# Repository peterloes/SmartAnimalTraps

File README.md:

# SmartAnimalTraps
Electrical applications for non-deadly animal traps built up with intelligent radio module, drive electronics for servomotors
(flap drive) and drive electronics for different low power light barriers.

Author: Loës P. (2022) 

## 1 RadiomoduleV1.0 & electronicsLightbarriers & electronicsServo
- Radio module V1.0 add-on board (not illustrated)
- Electronic light barriers for different distances.
- Servomotor and shutter is adjusted to the end positions.

The radio handheld transmitter is able to open and close the shutter by pressing a button.

Light barrier 1 and light barrier 2 are connected with logic AND. Both light barriers needs a falling edge of the signals to close the shutter. 
Light barrier 1 and light barrier 2 is forbidden to open the shutter.

Pushbutton 1 and pushbutton 2, mounted on the top of the electronical circuit, are able to open and close the shutter.

### Current consumption:

Standby 20.8mA@6V, clocked approx. 2.0mA@6V (after 10 minutes).

Operate mode 320mA@6V (max.)

### Application bird trap:

### Components:

https://github.com/peterloes/SmartAnimalTraps/blob/main/Getting_Started_Tutorial/13_wireless_radiomodule.JPG

https://github.com/peterloes/SmartAnimalTraps/blob/main/Schematics/radio_module_V1.0.brd.pdf

https://github.com/peterloes/Light_Barrier

https://github.com/peterloes/Servo_Engine

--> Protection against misuse!!! Dear follower, please contact me via email to get more information about the used wireless radio module. 

## 2 RadiomoduleV2.0 & electronicsServo
- Radio module V2.0 add-on board (not illustrated) 
- No light barriers
- Servomotor and shutter is adjusted to the end positions.

The radio handheld transmitter is able to open and close the shutter by pressing a button.

Pushbutton 1 and pushbutton 2, mounted on the top of the electronical circuit, are able to open and close the shutter.

### Current consumption:  

Standby 20.5mA@6V, clocked approx. 2.3mA@6V (after 10 minutes).

Operate mode 235mA@6V (max.)

### Components:

https://github.com/peterloes/SmartAnimalTraps/blob/main/Getting_Started_Tutorial/13_wireless_radiomodule.JPG

https://github.com/peterloes/SmartAnimalTraps/blob/main/Schematics/radio_module_V2.0.brd.pdf

https://github.com/peterloes/Servo_Engine

--> Protection against misuse!!! Dear follower, please contact me via email to get more information about the used wireless radio module. 

## 3 RadiomoduleV3.0 & modifiedServo
- Radio module V3.0 add-on board (Version from year 2010, to revision)
- No light barriers
- Full rotation of modified servomotor --> Motor rotation 360° --> left/right rotations

The radio handheld transmitter is able to open, close and to rotates the shutter by pressing a button.

### Current consumption:  

Standby 30mA@6V, clocked approx. 11.4mA@6V (after 10 minutes). With LEDs.

Operate mode 179mA@6V Motor is steady turning. With LEDs.

### Application:

https://github.com/peterloes/SmartAnimalTraps/blob/main/Getting_Started_Tutorial/Snaptrap.jpg

### Components:

https://github.com/peterloes/SmartAnimalTraps/blob/main/Getting_Started_Tutorial/13_wireless_radiomodule.JPG

https://github.com/peterloes/SmartAnimalTraps/blob/main/Schematics/radio_module_V3.0.brd.pdf

https://github.com/peterloes/SmartAnimalTraps/blob/main/Getting_Started_Tutorial/33_Servo_modified.JPG

https://github.com/peterloes/SmartAnimalTraps/blob/main/Getting_Started_Tutorial/34_old_batterypack.JPG

--> Protection against misuse!!! Dear follower, please contact me via email to get more information about the used wireless radio module. 

## 4 RadiomoduleV4.0 & reusedFrontplate & electronicsLightbarriers & electronicsServo
- Radio module V4.0 add-on board (not illustrated)
- Reused frontplate from nestbox included light barriers.
- Electronic light barriers.
- Servomotor and shutter is adjusted to the end positions.

The radio handheld transmitter is able to open and close the shutter by pressing a button.

Light barrier 1 and light barrier 2 are connected with logic AND. Both light barriers needs a falling edge of the signals to close the shutter.
Light barrier 1 and light barrier 2 is forbidden to open the shutter.

Pushbutton 1 and pushbutton 2, mounted on the top of the electronical circuit, are able to open and close the shutter.

### Current consumption:

Standby 21.9mA@6V, clocked approx. 3.5mA@6V (after 10 minutes). With LEDs.

Operate mode 303mA@6V (max.). With LEDs.

### Components:

https://github.com/peterloes/SmartAnimalTraps/blob/main/Getting_Started_Tutorial/13_wireless_radiomodule.JPG

https://github.com/peterloes/SmartAnimalTraps/blob/main/Schematics/radio_module_V4.0.brd.pdf

https://github.com/peterloes/Light_Barrier

https://github.com/peterloes/Servo_Engine

Frontplate nestbox

https://github.com/peterloes/RFID-MS

https://github.com/peterloes/SmartAnimalTraps/blob/main/Getting_Started_Tutorial/7_Supplier.txt

--> Protection against misuse!!! Dear follower, please contact me via email to get more information about the used wireless radio module. 

## 5 ElectronicsLightBarriers & electronicsServo
- No radio module
- Electronic light barriers for different distances are switching shutter positions.
- Servomotor and shutter is adjusted to the end positions.

Light barrier 1 or light barrier 2 are able to open or to close the shutter.

Pushbutton 1 or pushbutton 2, mounted on the top of the electronical circuit, are able to open or to close the shutter.

### Current consumption:

Standby 0,22mA@6V --> 220µA@6V

Operate mode 322mA@6V (max.)

### Components:

https://github.com/peterloes/Light_Barrier

https://github.com/peterloes/Servo_Engine

## 6 ReusedFrontplate & electronicsServo
- No radio module
- Reused frontplate from nestbox included light barriers. Switching shutter positions.
- Servomotor and shutter is adjusted to the end positions.

Light barrier 1 or light barrier 2 are able to open or to close the shutter.

Pushbutton 1 or pushbutton 2, mounted on the top of the electronical circuit, are able to open or to close the shutter.

### Current consumption:

Standby 0,05mA@6V --> 50µA@6V

Operate mode 375mA@6V (max.)

### Components:

https://github.com/peterloes/Servo_Engine

Frontplate nestbox

https://github.com/peterloes/RFID-MS

https://github.com/peterloes/SmartAnimalTraps/blob/main/Getting_Started_Tutorial/7_Supplier.txt

### EXTENSIONS

https://github.com/peterloes/SmartAnimalTraps/blob/main/Getting_Started_Tutorial/SailwinchServo.jpg

https://github.com/peterloes/SmartAnimalTraps/blob/main/Getting_Started_Tutorial/LightBarrier_example.jpg

https://hackaday.io/project/193448-solenoid-as-a-switch-with-proximity-detection

#### Intelligent radio module:

Wireless module receives and evaluates the data received from a transmitter.

In order to carry out a command from a transmitter, it must first be taught.
Teaching of a transmitter is carried out very easily by means of a button.
As required, up to 60 transmitters can be taught with all keys or individual transmission keys.
The particular highlight is the feedback from the receiver. You can see from the transmitter
whether the wireless communication was successful and receive information about the quality of the transmission path.
Electronical release range of 70 metres tested in urban environment. 

https://github.com/peterloes/SmartAnimalTraps/blob/main/Getting_Started_Tutorial/13_wireless_radiomodule.JPG

Examples after teaching the modules:
 
Hand-held transmitter --> Button1 -- Trap1 --> Shutter closed

Hand-held transmitter --> Button2 -- Trap1 --> Shutter open

Hand-held transmitter --> Button3 -- Trap2 --> Shutter closed

Hand-held transmitter --> Button4 -- Trap2 --> Shutter open

or 
 
Hand-held transmitter --> Button1 -- Trap1-Trap2-Trap3-Trap4 --> Shutter closed

Hand-held transmitter --> Button2 -- Trap1-Trap2-Trap3-Trap4 --> Shutter open

#### Drive electronics for servomotor and flap:

Trigger always the same positions over input signals (two end points) or over pushbuttons.

The servo setup procedure consists of 4 steps:

Adjust end position 1. This can be the most left or the most right end point. This position will be reached after power-up if valid servo data has been found in FLASH.
Adjust end position 2. This is the opposite end position to position 1.
Adjust servo speed. The servo permanently moves between the two end points. The speed can be adjusted via S1 and S2.
Asserting S3 the 4th time stores the servo parameters into FLASH and returns to normal operation

.https://github.com/peterloes/Servo_Engine

Examples for shutter positions after adjust the end positions:

Pushbutton 1 end position 1 --> Shutter open 

Pushbutton 2 end position 2 --> Shutter closed

or

Input signal 1 end position 1 --> Shutter open

Input signal 2 end position 2 --> Shutter closed

#### Drive electronics for light barriers:

Supported two low power light barriers, adjustable for different distances(size of animal) 10 centimetres to tested 3.3 metres. 
The beam is scattered light independently and invisible.
Wide power input range of light barrier circuit board 3.3V to max.60V. Used receiver from Vishay "TSSP58038" and LED from Vishay "VSLB3940"

https://github.com/peterloes/Light_Barrier

Examples for light barriers:

Light barrier 1 and light barrier 2 are connected with logic AND. Both light barriers needs a falling edge of the signals to close the shutter.

Light barrier 1 or light barrier 2 are able to open or to close the shutter.

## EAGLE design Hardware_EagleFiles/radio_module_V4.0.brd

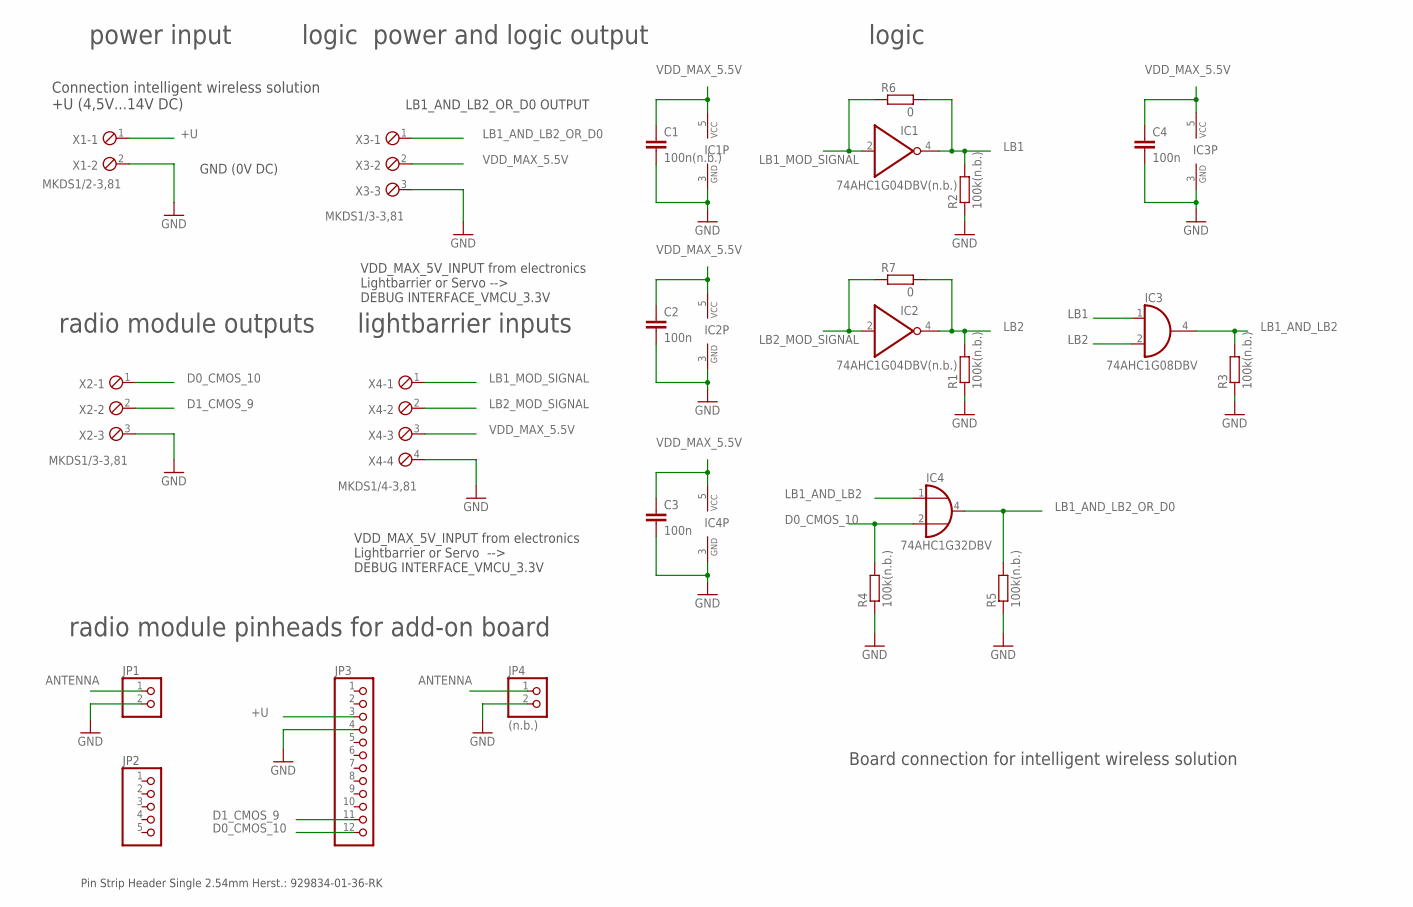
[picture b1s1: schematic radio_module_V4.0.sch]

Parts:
C1: 100n(n.b.); C0805
C2, C3, C4: 100n; C0805
IC1, IC2: 74AHC1G04DBV(n.b.); SOT23-5
IC3: 74AHC1G08DBV; SOT23-5
IC4: 74AHC1G32DBV; SOT23-5
JP1: PINHD-1X2; 1X02
JP2: PINHD-1X5; 1X05
JP3: PINHD-1X12; 1X12
JP4: (n.b.); 1X02
R1, R2, R3, R4, R5: 100k(n.b.); R0805
R6, R7: 0; R0805
X1: MKDS1/2-3,81; 2POL381
X2, X3: MKDS1/3-3,81; 3POL381
X4: MKDS1/4-3,81; 4POL381

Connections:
+U: JP3.3, X1.1
ANTENNA: JP1.1, JP4.1
D0_CMOS_10: IC4.2 (I1), JP3.12, R4.2, X2.1
D1_CMOS_9: JP3.11, X2.2
GND: C1.2, C2.2, C3.2, C4.2, IC1.3 (GND), IC2.3 (GND), IC3.3 (GND), IC4.3 (GND), JP1.2, JP3.4, JP4.2, R1.1, R2.1, R3.1, R4.1, R5.1, X1.2, X2.3, X3.3, X4.4
LB1: IC1.4 (O), IC3.1 (I0), R2.2, R6.2
LB1_AND_LB2: IC3.4 (O), IC4.1 (I0), R3.2
LB1_AND_LB2_OR_D0: IC4.4 (O), R5.2, X3.1
LB1_MOD_SIGNAL: IC1.2 (I), R6.1, X4.1
LB2: IC2.4 (O), IC3.2 (I1), R1.2, R7.2
LB2_MOD_SIGNAL: IC2.2 (I), R7.1, X4.2
VDD_MAX_5.5V: C1.1, C2.1, C3.1, C4.1, IC1.5 (VCC), IC2.5 (VCC), IC3.5 (VCC), IC4.5 (VCC), X3.2, X4.3

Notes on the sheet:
Board connection for intelligent wireless solution
power input
Connection intelligent wireless solution +U (4,5V...14V DC)
GND (0V DC)
Pin Strip Header Single 2.54mm Herst.: 929834-01-36-RK
radio module pinheads for add-on board
radio module outputs
lightbarrier inputs
logic power and logic output
logic
LB1_AND_LB2_OR_D0 OUTPUT
VDD_MAX_5V_INPUT from electronics Lightbarrier or Servo --> DEBUG INTERFACE_VMCU_3.3V
VDD_MAX_5V_INPUT from electronics Lightbarrier or Servo --> DEBUG INTERFACE_VMCU_3.3V

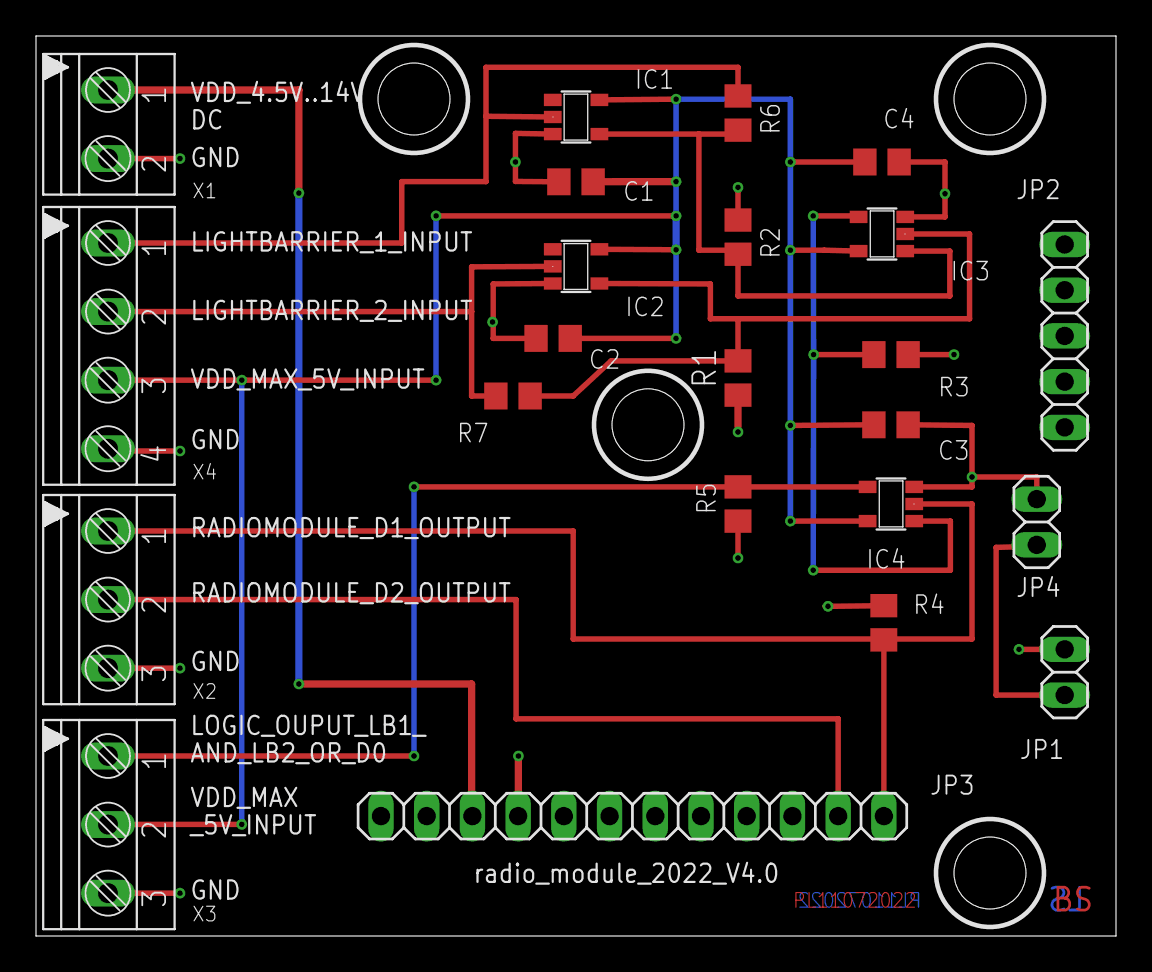
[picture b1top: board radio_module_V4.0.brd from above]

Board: 4 copper layers, 60.0 x 50.0 mm, 23 parts (0 on the bottom side), 12 nets.

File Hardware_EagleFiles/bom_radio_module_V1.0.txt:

Stückliste exportiert aus C:/MPIO/TECHNIK/HARDWARE/EAGLE_FILES/Wireless_Servo_2022/radio_module_V1.0.sch am 07.07.2022 10:13

Part Value        Device       Package Description                                              
C1   100n         C-EUC0805    C0805   CAPACITOR, European symbol                               
C2   100n         C-EUC0805    C0805   CAPACITOR, European symbol                               
C3   100n         C-EUC0805    C0805   CAPACITOR, European symbol                               
C4   100n         C-EUC0805    C0805   CAPACITOR, European symbol                               
IC1  74AHC1G04DBV 74AHC1G04DBV SOT23-5 INVERTER Gate                                            
IC2  74AHC1G04DBV 74AHC1G04DBV SOT23-5 INVERTER Gate                                            
IC3  74AHC1G08DBV 74AHC1G08DBV SOT23-5 2-input AND gate                                         
IC4  74AHC1G32DBV 74AHC1G32DBV SOT23-5 2-input OR gate                                          
JP1               PINHD-1X2    1X02    PIN HEADER (Pin Strip Header Single 2.54mm Herst.: 929834-01-36-RK)                                              
JP2               PINHD-1X5    1X05    PIN HEADER (Pin Strip Header Single 2.54mm Herst.: 929834-01-36-RK)                                              
JP3               PINHD-1X12   1X12    PIN HEADER (Pin Strip Header Single 2.54mm Herst.: 929834-01-36-RK)                                              
JP4  (n.b.)       PINHD-1X2    1X02    PIN HEADER                                               
R1   100k(n.b.)   R-EU_R0805   R0805   RESISTOR, European symbol                                
R2   100k(n.b.)   R-EU_R0805   R0805   RESISTOR, European symbol                                
R3   100k(n.b.)   R-EU_R0805   R0805   RESISTOR, European symbol                                
R4   100k(n.b.)   R-EU_R0805   R0805   RESISTOR, European symbol                                
R5   100k(n.b.)   R-EU_R0805   R0805   RESISTOR, European symbol                                
X1   MKDS1/2-3,81 MKDS1/2-3,81 2POL381 MKDS 1/2-3,81 - Order No. 1727010 (RS-Online - 101-5384) 
X2   MKDS1/3-3,81 MKDS1/3-3,81 3POL381 MKDS 1/3-3,81 - Order No. 1727023 (RS-Online - 101-5390) 
X3   MKDS1/3-3,81 MKDS1/3-3,81 3POL381 MKDS 1/3-3,81 - Order No. 1727023 (RS-Online - 101-5390) 
X4   MKDS1/4-3,81 MKDS1/4-3,81 4POL381 MKDS 1/4-3,81 - Order No. 1727036

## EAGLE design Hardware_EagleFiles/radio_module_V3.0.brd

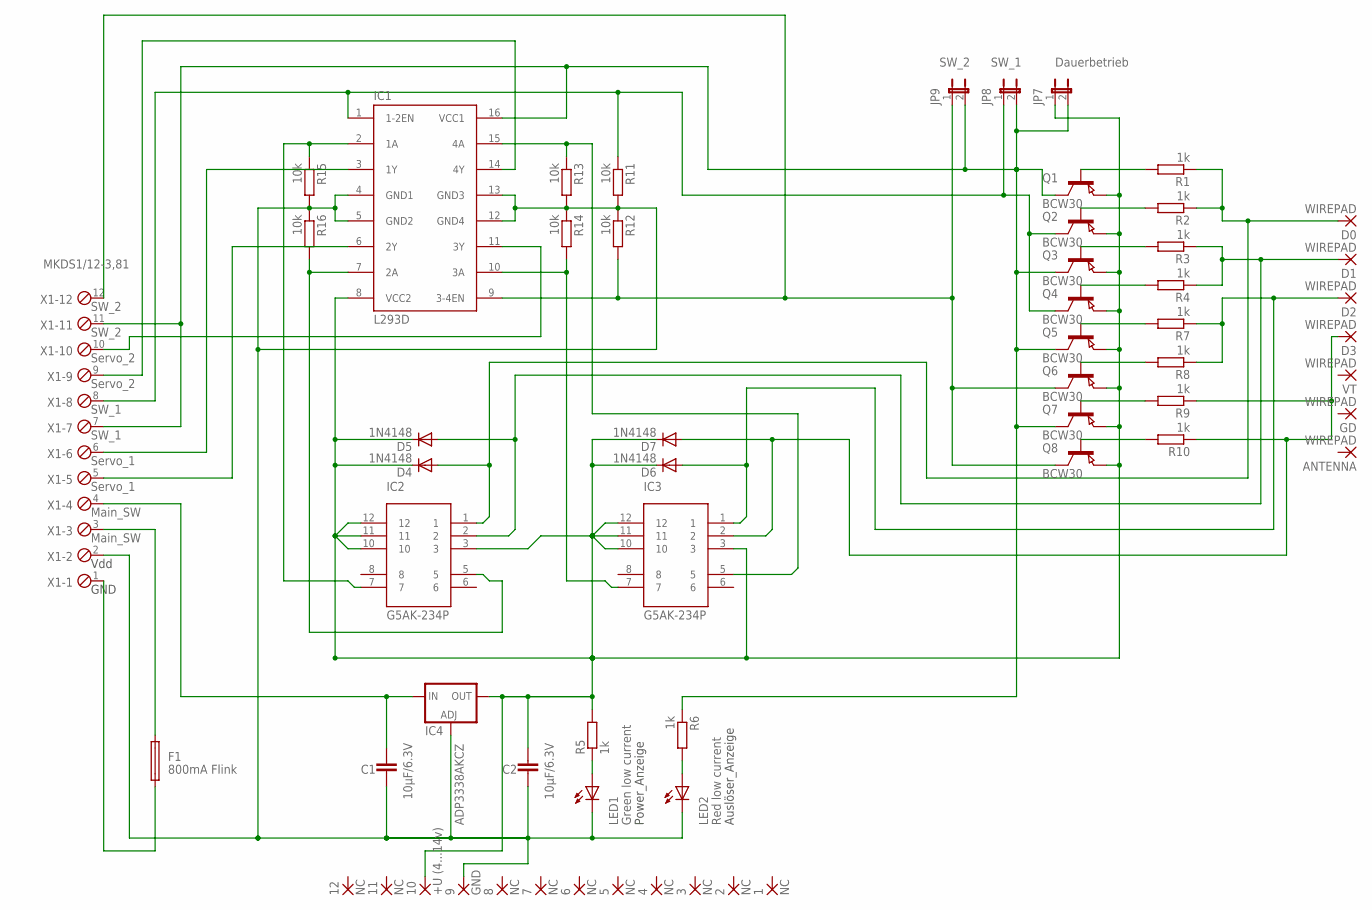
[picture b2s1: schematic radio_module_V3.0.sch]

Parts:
1, 2, 3, 4, 5, 6, 7, 8, 11, 12: NC; 1,6/0,9
9: GND; 1,6/0,9
10: +U (4...14v); 1,6/0,9
ANTENNA: WIREPAD; 1,6/0,9
C1, C2: 10µF/6.3V; C0805
D0, D1, D2, D3: WIREPAD; 1,6/0,9
D4, D5, D6, D7: 1N4148; DO35-7
F1: 800mA Flink; 19560
GD: WIREPAD; 1,6/0,9
IC1: L293D; DIL16
IC2, IC3: G5AK-234P
IC4: ADP3338AKCZ; SOT223
JP7: Dauerbetrieb; JP1
JP8: SW_1; JP1
JP9: SW_2; JP1
LED1: Green low current; LED3MM
LED2: Red low current; LED3MM
Q1, Q2, Q3, Q4, Q5, Q6, Q7, Q8: BCW30; SOT23
R1, R2, R3, R4, R5, R6, R7, R8, R9, R10: 1k; R0402
R11, R12, R13, R14, R15, R16: 10k; R0402
VT: WIREPAD; 1,6/0,9
X1: MKDS1/12-3,81; 12POL381

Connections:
GND: 9.1, C1.2, C2.2, IC1.4 (GND1), IC1.5 (GND2), IC1.12 (GND4), IC1.13 (GND3), IC4.1 (ADJ), LED1.K (C), LED2.K (C), R11.2, R12.1, R13.2, R14.1, R15.2, R16.1, X1.2
unnamed: IC1.3 (1Y), X1.6
unnamed: IC1.6 (2Y), X1.5
unnamed: IC1.7 (2A), IC2.5, R16.2
unnamed: IC1.11 (3Y), X1.10
unnamed: Q1.1 (B), R1.2
unnamed: Q3.1 (B), R3.2
unnamed: Q5.1 (B), R7.2
unnamed: Q7.1 (B), R9.2
unnamed: Q2.1 (B), R2.2
unnamed: Q4.1 (B), R4.2
unnamed: Q6.1 (B), R8.2
unnamed: Q8.1 (B), R10.2
unnamed: IC1.16 (VCC1), JP7.2, JP8.2, JP9.2, Q1.3 (C), Q3.3 (C), Q5.3 (C), Q7.3 (C), R6.1, X1.7, X1.11
unnamed: IC1.2 (1A), IC2.7, R15.1
unnamed: D0.1, D4.A, IC2.1, R1.1, R2.1
unnamed: LED2.A, R6.2
unnamed: F1.1, X1.1
unnamed: D1.1, D5.A, IC2.2, R3.1, R4.1
unnamed: IC1.14 (4Y), X1.9
unnamed: F1.2, X1.3
unnamed: D3.1, D7.A, IC3.2, R9.1, R10.1
unnamed: IC1.10 (3A), IC3.7, R14.2
unnamed: IC1.15 (4A), IC3.5, R13.1
unnamed: C1.1, IC4.3 (IN), X1.4
unnamed: LED1.A, R5.1
unnamed: D2.1, D6.A, IC3.1, R7.1, R8.1
unnamed: IC1.1 (1-2EN), JP8.1, Q2.3 (C), Q4.3 (C), R11.1, X1.8
unnamed: IC1.9 (3-4EN), JP9.1, Q6.3 (C), Q8.3 (C), R12.2, X1.12
VDD: 10.1, C2.1, D4.C, D5.C, D6.C, D7.C, IC1.8 (VCC2), IC2.3, IC2.10, IC2.11, IC2.12, IC3.3, IC3.10, IC3.11, IC3.12, IC4.4 (OUT), JP7.1, Q1.2 (E), Q2.2 (E), Q3.2 (E), Q4.2 (E), Q5.2 (E), Q6.2 (E), Q7.2 (E), Q8.2 (E), R5.2

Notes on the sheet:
Vdd
GND
SW_1
SW_2
Auslöser_Anzeige
Power_Anzeige
Main_SW
Servo_1
Servo_2

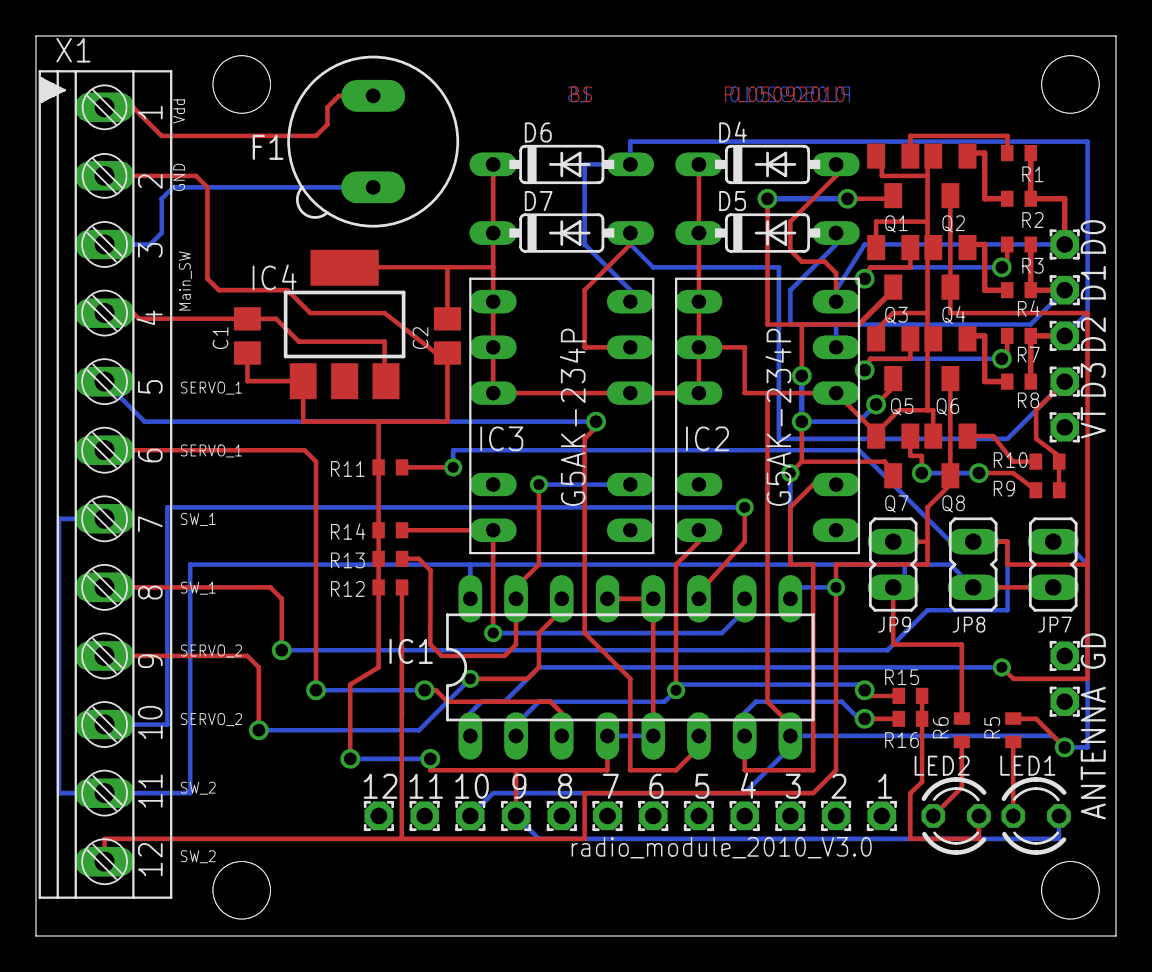
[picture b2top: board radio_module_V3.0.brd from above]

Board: 2 copper layers, 60.0 x 50.0 mm, 60 parts (0 on the bottom side), 30 nets.

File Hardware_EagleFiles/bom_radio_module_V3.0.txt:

Part    Value             Device               Package   Description                                                   
1       NC                1,6/0,9              1,6/0,9   THROUGH-HOLE PAD Pin Strip Header Single 2.54mm Herst.: 929834-01-36-RK                                              
2       NC                1,6/0,9              1,6/0,9   THROUGH-HOLE PAD                                              
3       NC                1,6/0,9              1,6/0,9   THROUGH-HOLE PAD                                              
4       NC                1,6/0,9              1,6/0,9   THROUGH-HOLE PAD                                              
5       NC                1,6/0,9              1,6/0,9   THROUGH-HOLE PAD                                              
6       NC                1,6/0,9              1,6/0,9   THROUGH-HOLE PAD                                              
7       NC                1,6/0,9              1,6/0,9   THROUGH-HOLE PAD                                              
8       NC                1,6/0,9              1,6/0,9   THROUGH-HOLE PAD                                              
9       GND               1,6/0,9              1,6/0,9   THROUGH-HOLE PAD                                              
10      +U (4...14v)      1,6/0,9              1,6/0,9   THROUGH-HOLE PAD                                              
11      NC                1,6/0,9              1,6/0,9   THROUGH-HOLE PAD                                              
12      NC                1,6/0,9              1,6/0,9   THROUGH-HOLE PAD                                              
ANTENNA WIREPAD           1,6/0,9              1,6/0,9   THROUGH-HOLE PAD                                              
C1      10µF/6.3V         C-EUC0805            C0805     CAPACITOR, European symbol                                    
C2      10µF/6.3V         C-EUC0805            C0805     CAPACITOR, European symbol                                    
D0      WIREPAD           1,6/0,9              1,6/0,9   THROUGH-HOLE PAD Pin Strip Header Single 2.54mm Herst.: 929834-01-36-RK                                             
D1      WIREPAD           1,6/0,9              1,6/0,9   THROUGH-HOLE PAD                                              
D2      WIREPAD           1,6/0,9              1,6/0,9   THROUGH-HOLE PAD                                              
D3      WIREPAD           1,6/0,9              1,6/0,9   THROUGH-HOLE PAD                                              
D4      1N4148            1N4148DO35-7         DO35-7    DIODE                                                         
D5      1N4148            1N4148DO35-7         DO35-7    DIODE                                                         
D6      1N4148            1N4148DO35-7         DO35-7    DIODE                                                         
D7      1N4148            1N4148DO35-7         DO35-7    DIODE                                                         
F1      800mA Flink       FUSE19560            19560     Fuse                                                          
GD      WIREPAD           1,6/0,9              1,6/0,9   THROUGH-HOLE PAD                                              
IC1     L293D             L293D                DIL16     PUSH-PULL 4 CHANNEL DRIVER                                    
IC2     G5AK-234P         G5AK-234P            G5AK-234P                                                               
IC3     G5AK-234P         G5AK-234P            G5AK-234P                                                               
IC4     ADP3338AKCZ       LD117AS12TR          SOT223    Low drop fixed and adjustable positive voltage regulators 1 A 
JP7     Dauerbetrieb      JP1E                 JP1       JUMPER                                                        
JP8     SW_1              JP1E                 JP1       JUMPER                                                        
JP9     SW_2              JP1E                 JP1       JUMPER                                                        
LED1    Green low current LED3MM               LED3MM    LED                                                           
LED2    Red low current   LED3MM               LED3MM    LED                                                           
Q1      BCW30             PNP-TRANSISTOR_SOT23 SOT23     PNP TRANSISTOR                                                
Q2      BCW30             PNP-TRANSISTOR_SOT23 SOT23     PNP TRANSISTOR                                                
Q3      BCW30             PNP-TRANSISTOR_SOT23 SOT23     PNP TRANSISTOR                                                
Q4      BCW30             PNP-TRANSISTOR_SOT23 SOT23     PNP TRANSISTOR                                                
Q5      BCW30             PNP-TRANSISTOR_SOT23 SOT23     PNP TRANSISTOR                                                
Q6      BCW30             PNP-TRANSISTOR_SOT23 SOT23     PNP TRANSISTOR                                                
Q7      BCW30             PNP-TRANSISTOR_SOT23 SOT23     PNP TRANSISTOR                                                
Q8      BCW30             PNP-TRANSISTOR_SOT23 SOT23     PNP TRANSISTOR                                                
R1      1k                R-EU_R0402           R0402     RESISTOR, European symbol                                     
R2      1k                R-EU_R0402           R0402     RESISTOR, European symbol                                     
R3      1k                R-EU_R0402           R0402     RESISTOR, European symbol                                     
R4      1k                R-EU_R0402           R0402     RESISTOR, European symbol                                     
R5      1k                R-EU_R0402           R0402     RESISTOR, European symbol                                     
R6      1k                R-EU_R0402           R0402     RESISTOR, European symbol                                     
R7      1k                R-EU_R0402           R0402     RESISTOR, European symbol                                     
R8      1k                R-EU_R0402           R0402     RESISTOR, European symbol                                     
R9      1k                R-EU_R0402           R0402     RESISTOR, European symbol                                     
R10     1k                R-EU_R0402           R0402     RESISTOR, European symbol                                     
R11     10k               R-EU_R0402           R0402     RESISTOR, European symbol                                     
R12     10k               R-EU_R0402           R0402     RESISTOR, European symbol                                     
R13     10k               R-EU_R0402           R0402     RESISTOR, European symbol                                     
R14     10k               R-EU_R0402           R0402     RESISTOR, European symbol                                     
R15     10k               R-EU_R0402           R0402     RESISTOR, European symbol                                     
R16     10k               R-EU_R0402           R0402     RESISTOR, European symbol                                     
VT      WIREPAD           1,6/0,9              1,6/0,9   THROUGH-HOLE PAD Pin Strip Header Single 2.54mm Herst.: 929834-01-36-RK                                             
X1      MKDS1/12-3,81     MKDS1/12-3,81        12POL381  MKDS 1/12-3,81 - Order No. 1727117
